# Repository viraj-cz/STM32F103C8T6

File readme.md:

### Schematic

------------------------------
### Footprint Assignment

------------------------------
### DRC (for JLCPCB)

------------------------------
### Layout (WIP)

------------------------------
[Reference](https://youtu.be/aVUqaB0IMh4)

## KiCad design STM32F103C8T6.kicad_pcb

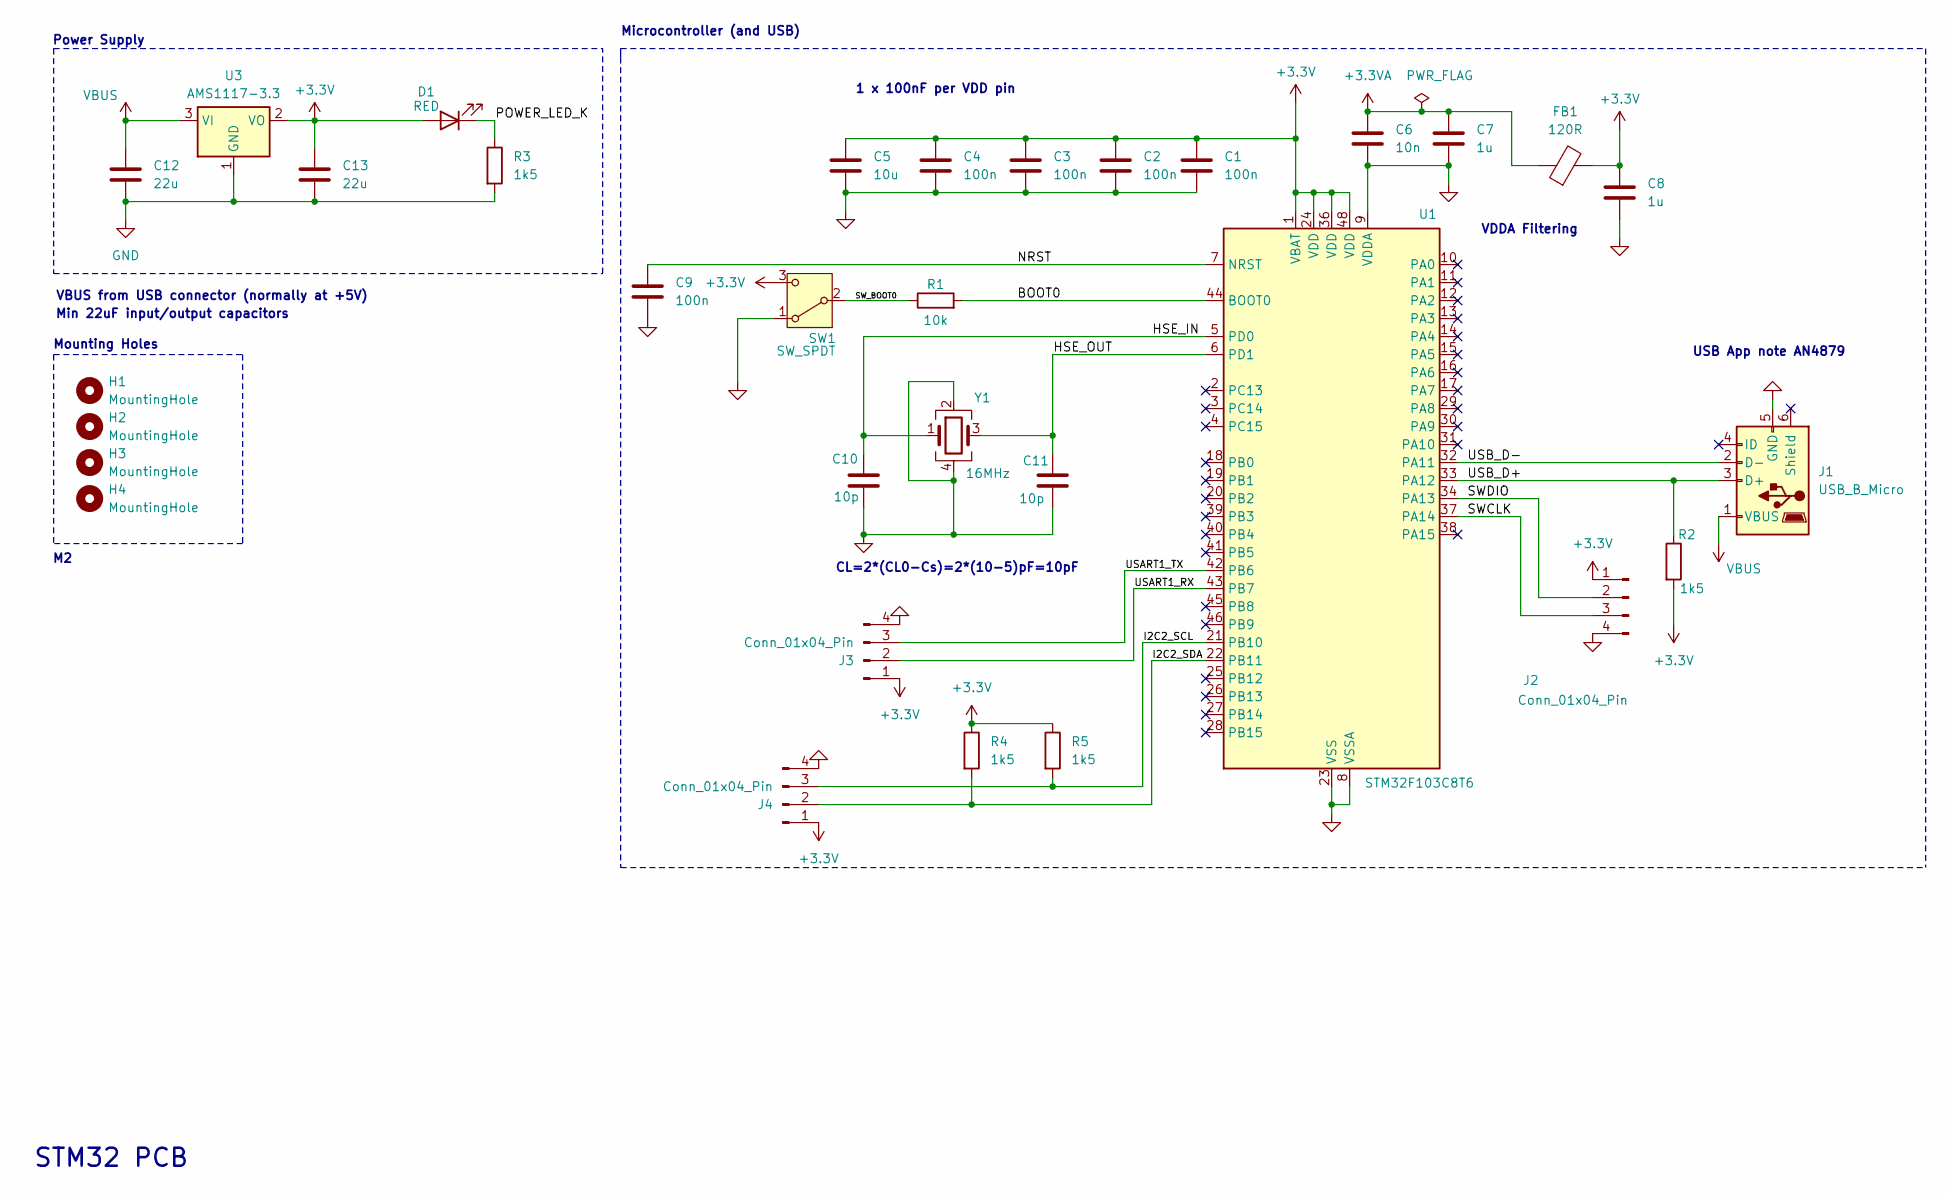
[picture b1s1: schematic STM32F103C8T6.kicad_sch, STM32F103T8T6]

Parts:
C1, C2, C3, C4, C9: 100n; C_0402_1005Metric
C5: 10u; C_0603_1608Metric
C6: 10n; C_0402_1005Metric
C7, C8: 1u; C_0402_1005Metric
C10, C11: 10p; C_0402_1005Metric
C12, C13: 22u; C_0805_2012Metric
D1: RED; LED_0603_1608Metric
FB1: 120R; L_0603_1608Metric
H1, H2, H3, H4: MountingHole; MountingHole_2.2mm_M2
J1: USB_B_Micro; USB_Micro-B_Wuerth_629105150521
J2, J3, J4: Conn_01x04_Pin; PinHeader_1x04_P2.54mm_Vertical
R1: 10k; R_0402_1005Metric
R2, R3, R4, R5: 1k5; R_0402_1005Metric
SW1: SW_SPDT; SW_SPDT_PCM12
U1: STM32F103C8T6; LQFP-48_7x7mm_P0.5mm
U3: AMS1117-3.3; SOT-223-3_TabPin2
Y1: 16MHz; Crystal_SMD_3225-4Pin_3.2x2.5mm

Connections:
+3.3V: C1.1, C2.1, C3.1, C4.1, C5.1, C8.1, C13.1, D1.2 (A), FB1.2, J2.1, J3.1, J4.1, R2.2, R4.1, R5.1, SW1.3 (C), U1.1 (VBAT), U1.24 (VDD), U1.36 (VDD), U1.48 (VDD), U3.2 (VO)
+3.3VA: C6.1, C7.1, FB1.1
/ NRST: C9.1, U1.7 (NRST)
/BOOT0: R1.2, U1.44 (BOOT0)
/HSE_IN: C10.1, U1.5 (PD0), Y1.1
/HSE_OUT: C11.1, U1.6 (PD1), Y1.3
/I2C2_SCL: J4.3, R5.2, U1.21 (PB10)
/I2C2_SDA: J4.2, R4.2, U1.22 (PB11)
/POWER_LED_K: D1.1 (K), R3.1
/SWCLK: J2.3, U1.37 (PA14)
/SWDIO: J2.2, U1.34 (PA13)
/SW_BOOT0: R1.1, SW1.2 (B)
/USART1_RX: J3.2, U1.43 (PB7)
/USART1_TX: J3.3, U1.42 (PB6)
/USB_D+: J1.3 (D+), R2.1, U1.33 (PA12)
/USB_D-: J1.2 (D-), U1.32 (PA11)
GND: C1.2, C2.2, C3.2, C4.2, C5.2, C6.2, C7.2, C8.2, C9.2, C10.2, C11.2, C12.2, C13.2, J1.5 (GND), J2.4, J3.4, J4.4, R3.2, SW1.1 (A), U1.8 (VSSA), U1.9 (VDDA), U1.23 (VSS), U1.35 (VSS), U1.47 (VSS), U3.1 (GND), Y1.2, Y1.4
VBUS: C12.1, J1.1 (VBUS), U3.3 (VI)

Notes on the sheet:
STM32 PCB
Min 22uF input/output capacitors
USB App note AN4879
VBUS from USB connector (normally at +5V)
Power Supply
1 x 100nF per VDD pin
VDDA Filtering
Microcontroller (and USB)
CL=2*(CL0-Cs)=2*(10-5)pF=10pF
Mounting Holes

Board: 2 copper layers, 32 parts (0 on the bottom side), 18 nets, no tracks yet.

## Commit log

2025-05-05 started
2025-05-11 schematic done
2025-05-11 footprint assigned
2025-05-12 DRC setup
2025-05-15 footprint corrected, layout started
2025-05-18 footprint changes, WIP layout
